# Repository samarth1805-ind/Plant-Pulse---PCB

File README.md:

# 🌱 Plant Pulse - Smart Plant Monitoring PCB

A custom **two-layer PCB** designed in **KiCad** for the **Plant Pulse** smart plant monitoring system.

This project integrates multiple sensors with an ESP32 microcontroller to monitor soil moisture and environmental conditions while efficiently managing power distribution. The PCB is designed to provide a compact, organized, and reliable hardware platform for an automated plant care system.

---

## 📖 Project Overview

Plant Pulse is an automated plant monitoring system that continuously observes the condition of multiple plants using dedicated sensors. The collected data is processed by an **ESP32** microcontroller, allowing the system to make informed decisions regarding plant health and maintenance.

This repository contains the custom PCB design created in **KiCad**, including the schematic, PCB layout, and 3D visualization.

---

## ✨ Features

- 🌿 Supports multiple soil moisture sensors
- 🌡️ Atmospheric sensor interface
- ⚡ ESP32-based controller
- 🔋 LiPo battery powered
- ⏱️ Power Timer for efficient power management
- 🛠️ Custom two-layer PCB
- 📐 Designed using KiCad
- 🎨 3D PCB visualization

---

## 🔧 Components Used

| Component | Purpose |
|-----------|---------|
| ESP32 | Main microcontroller |
| Soil Moisture Sensors | Monitor soil moisture of multiple plants |
| Atmospheric Sensor | Measures environmental conditions |
| Power Timer | Controls power distribution |
| LiPo Battery | Portable power source |
| Resistors | Signal conditioning and pull-up/pull-down connections |
| Pin Headers | External sensor connections |

---

## 🛠️ Software Used

- **KiCad** – PCB Design
- Git & GitHub – Version Control

---

## 📂 Repository Structure

```
Plant-Pulse
│
├── PCB
│   ├── plants_plot.kicad_pcb
│   └── plants_plot.kicad_pro
│
├── Schematic
│   └── plants_plot.kicad_sch
│
├── Images
│   ├── PCB_Layout.png
│   ├── 3D_Front.png
│   ├── 3D_Angle.png
│   ├── Schematic.png
│   └── Render.png
│
└── README.md
```

---

## 📸 PCB Design

### PCB Layout

> *
*
> *
*

```
Images/PCB_Layout.png
```

---

### 3D View

> *
*

```
Images/PCB_3D_Front.png

```

---

## 🎯 My Contribution

For this project, I:

- Created the PCB schematic in KiCad
- Designed a custom two-layer PCB
- Created a custom ESP32 footprint by referring to the project requirements
- Arranged and connected all PCB components
- Performed Design Rule Checks (DRC)
- Generated the 3D PCB model
- Organized the project for GitHub documentation

---

## 📚 Reference

This PCB design was created by following and learning from the following tutorial:

**Plant Pulse PCB Design**

https://youtu.be/TvA4ut0o4bc?si=sv90deI7XG99VpuN

The PCB presented in this repository is my own implementation created as a learning project using KiCad while following the concepts demonstrated in the tutorial.

---

## 🚀 Future Improvements

- Complete PCB routing
- PCB manufacturing
- Assembly and soldering
- Hardware testing
- Firmware development for ESP32
- Integration with IoT dashboard

---

## 👨‍💻 Author

**Samarth Prashant Pai**

Electronics & Telecommunication Engineering Student

GitHub: https://github.com/samarth1805-ind

---

### ⭐ If you found this project helpful, consider giving it a star!

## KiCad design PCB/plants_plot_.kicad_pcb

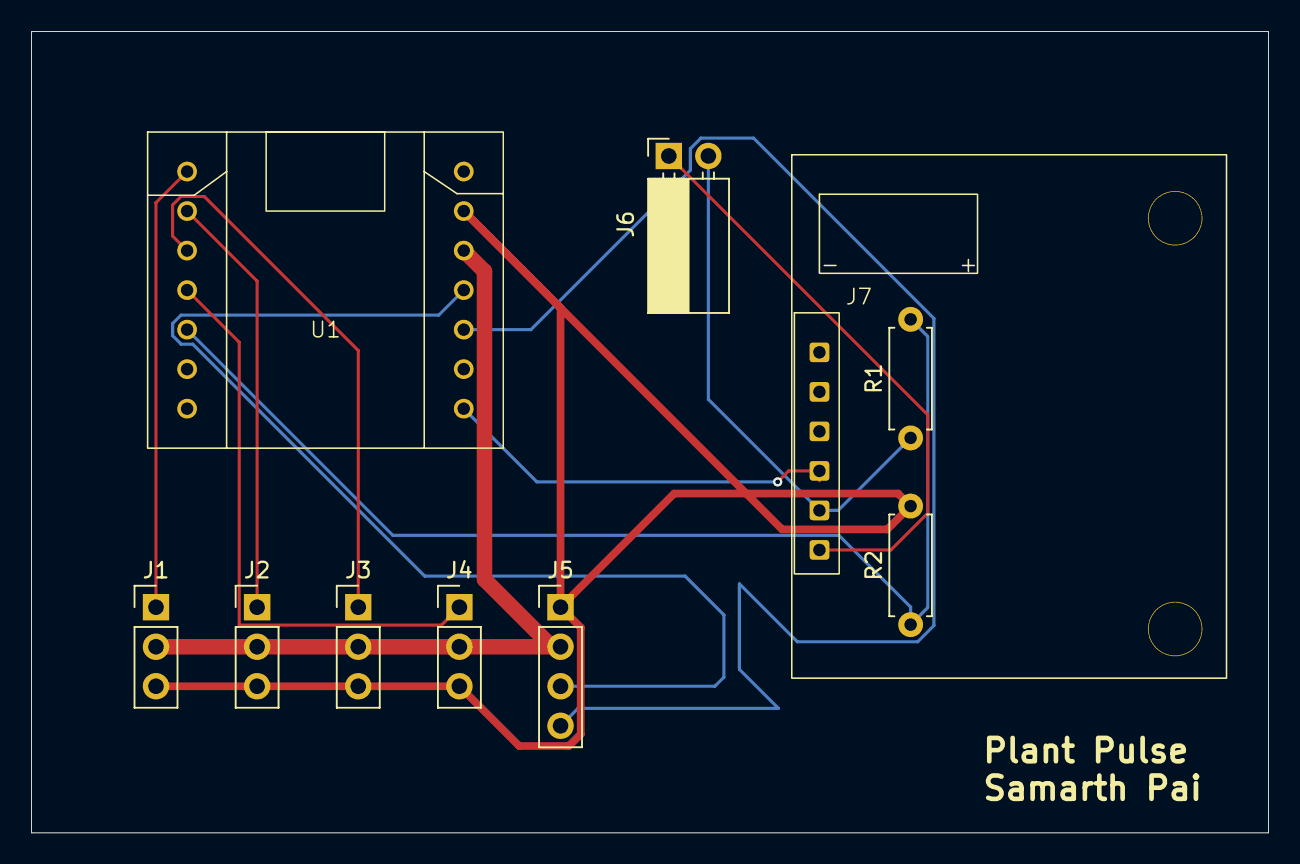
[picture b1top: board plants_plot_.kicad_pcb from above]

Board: 2 copper layers, 79.5 x 51.5 mm, 10 parts (0 on the bottom side), 12 nets.

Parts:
J1: Soil 1; PinHeader_1x03_P2.54mm_Vertical
J2: Soil 2; PinHeader_1x03_P2.54mm_Vertical
J3: Soil 3; PinHeader_1x03_P2.54mm_Vertical
J4: Soil 4; PinHeader_1x03_P2.54mm_Vertical
J5: Atmo; PinHeader_1x04_P2.54mm_Vertical
J6: BATT; PinSocket_1x02_P2.54mm_Horizontal
J7: PowerTimer
R1, R2: 10K; R_Axial_DIN0207_L6.3mm_D2.5mm_P7.62mm_Horizontal
U1: ESP32

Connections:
/Soil1_signal: J1.1, U1.1 (GP1)
unnamed: J1.2, J2.2, J3.2, J4.2, J5.2, U1.10 (3V3)
unnamed: J1.3, J2.3, J3.3, J4.3, J5.1, R2.2, U1.9 (GND)
unnamed: J2.1, U1.2 (GP2)
unnamed: J3.1, U1.3 (GP3)
unnamed: J4.1, U1.4 (GP4)
unnamed: J5.3, U1.11 (GP9)
unnamed: J5.4, U1.12 (GP8)
unnamed: J6.1, J7.6
unnamed: J6.2, J7.5, R1.1
unnamed: J7.4, U1.14 (GP44)
unnamed: R1.2, R2.1, U1.5 (GP5)
